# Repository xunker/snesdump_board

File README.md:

SNESDump Board
==============

A board for use with [https://github.com/cthill/SNESDump].

It is designed completely with through-hole components because that's what most people have lying
around.

The routing is _ugly_ because I wanted the board to be compatible with the original code without any
changes.

 ![Picture of rear of
board](images/snesdump_rear.jpg)

## Bill of Materials

* Cartridge Slot (1)
  - The cartridge slot can be either
    * A scavenged slot from a real SNES or Super-Famicom
    * A compatible 2.5mm 70-pin slot can be used with the appropriate pins yanked out
      - This slot *MUST* be 2.5mm pitch (so-called "metric spacing") and not the more common 2.54mm
    pitch (0.1 inches)

* Resistors (8)
  - Any 10K resistors will work as long as they can physically fit

* Shift Registers (3)
  - Any through-hole 74HC595N or compatible will work
  - Use of DIP sockets is recommended to make troubleshooting easier

* Arduino/Microcontroller
  - You can use either an Arduino Nano or Arduino Pro Micro (or clones thereof) in the indicated
    footprint
  - For obvious reasons you can't use both at the same time
  - It is **highly** recommended to mount the microcontroller on headers so it can be removed later

* Decoupling Capacitor (optional)
  - an electrolytic capacitor with a rating of at least 6.3v and a value from 0.1uF to 10uF will
    improve the general stability of the reader

## Licenses

SNES Slot Footprint ([SNES-CONN-EXP.kicad_mod](https://github.com/db-electronics/kicadlib)) is
distributed under the terms of CERN OHL v.1.2.

Arduino Pro Mini symbol and footprint (used as reference, not in final board output) is from
[SnapEDA](https://www.snapeda.com/parts/Arduino%20Pro%20Mini/Arduino/view-part/) and distributed
under [their license](footprints/SnapEDA+License.txt).

Unless otherwise specified, all other content herein is (C) 2022 Matthew Nielsen and is distributed
under the terms of [CC BY-NC-SA 4.0](https://creativecommons.org/licenses/by-nc-sa/4.0/).

### Sale of this board is NOT ALLOWED

I'm annoyed that I need to write this, but I do:

> ❗ ANY SALE OF THIS DESIGN IS STRICTLY PROHIBITED UNLESS AUTHORIZED IN WRITING BY RIGHTS HOLDER
>
> You **ARE ALLOWED** to make copies of this board for your __personal__ use, __give__ them to your
> friends, hand them out __for free__ to strangers on the street, or any other purpose so long as
> *you neither ask for nor receive payment* of any kind.
>
> You **ARE NOT ALLOWED** to make copies and sell them. Period. Whether you sell them for a profit
> or for a loss, it is not allowed. Whether you charge "for materials", "for time/labour", "for
> shipping and handling", it is not allowed.

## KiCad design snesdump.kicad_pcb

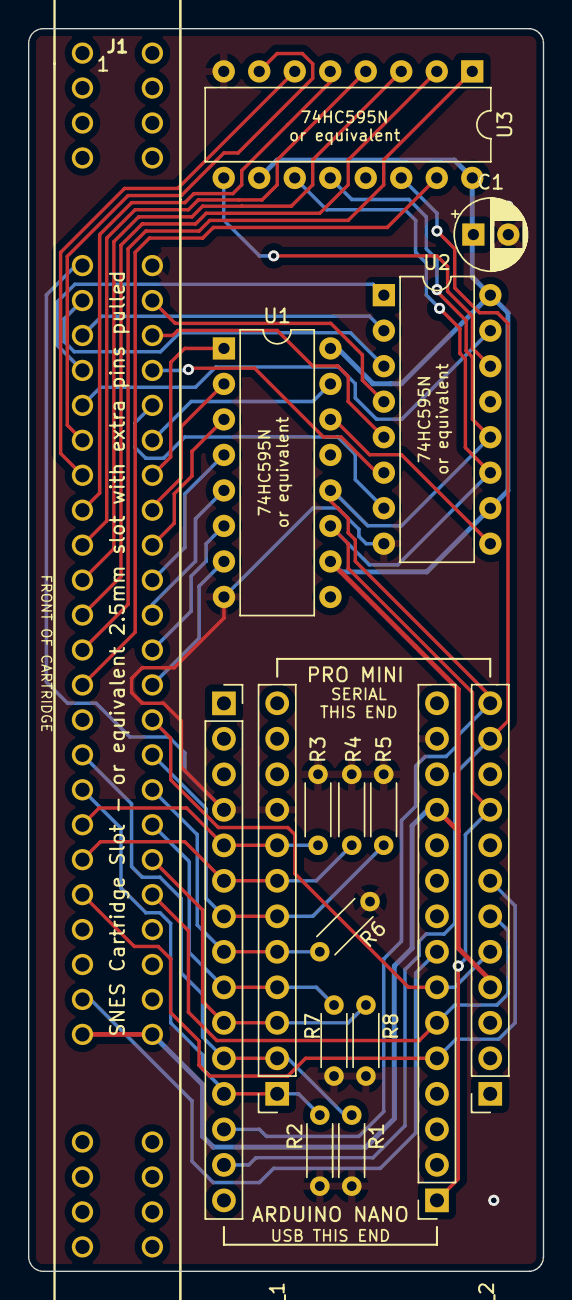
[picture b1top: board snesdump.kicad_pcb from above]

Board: 2 copper layers, 36.8 x 88.9 mm, 17 parts (0 on the bottom side), 43 nets.

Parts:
C1: 0.47uF; CP_Radial_D5.0mm_P2.50mm
J1: CARTRIDGE_SLOT; SNES-CONN-EXP
NANO_1, NANO_2: Conn_01x15_Male; PinSocket_1x15_P2.54mm_Vertical
PRO_MINI_1, PRO_MINI_2: Conn_01x12_Male; PinSocket_1x12_P2.54mm_Vertical
R1, R2, R3, R4, R5, R6, R7, R8: 10K; R_Axial_DIN0204_L3.6mm_D1.6mm_P5.08mm_Horizontal
U1, U2, U3: 74HC595; DIP-16_W7.62mm

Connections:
+5V: C1.1, J1.27, J1.58, NANO_2.12, PRO_MINI_2.4, U1.10 (~SRCLR), U1.16 (VCC), U2.10 (~SRCLR), U2.16 (VCC), U3.10 (~SRCLR), U3.16 (VCC)
A00: J1.17, U3.15 (QA)
A01: J1.16, U3.1 (QB)
A02: J1.15, U3.2 (QC)
A03: J1.14, U3.3 (QD)
A04: J1.13, U3.4 (QE)
A05: J1.12, U3.5 (QF)
A06: J1.11, U3.6 (QG)
A07: J1.10, U3.7 (QH)
A08: J1.9, U2.15 (QA)
A09: J1.8, U2.1 (QB)
A10: J1.7, U2.2 (QC)
A11: J1.6, U2.3 (QD)
A12: J1.37, U2.4 (QE)
A13: J1.38, U2.5 (QF)
A14: J1.39, U2.6 (QG)
A15: J1.40, U2.7 (QH)
BA0: J1.41, U1.15 (QA)
BA1: J1.42, U1.1 (QB)
BA2: J1.43, U1.2 (QC)
BA3: J1.44, U1.3 (QD)
BA4: J1.45, U1.4 (QE)
BA5: J1.46, U1.5 (QF)
BA6: J1.47, U1.6 (QG)
BA7: J1.48, U1.7 (QH)
D0: J1.19, NANO_1.11, PRO_MINI_1.2, R1.1
D1: J1.20, NANO_1.12, PRO_MINI_1.1, R2.1
D2: J1.21, NANO_1.5, PRO_MINI_1.8, R3.1
D3: J1.22, NANO_1.6, PRO_MINI_1.7, R4.1
D4: J1.50, NANO_1.7, PRO_MINI_1.6, R5.1
D5: J1.51, NANO_1.8, PRO_MINI_1.5, R6.1
D6: J1.52, NANO_1.9, PRO_MINI_1.4, R7.1
D7: J1.53, NANO_1.10, PRO_MINI_1.3, R8.1
GND: C1.2, J1.5, J1.36, NANO_1.4, NANO_2.14, PRO_MINI_1.9, R1.2, R2.2, R3.2, R4.2, R5.2, R6.2, R7.2, R8.2, U1.8 (GND), U2.8 (GND), U3.8 (GND)
RCK: NANO_1.13, PRO_MINI_2.12, U1.12 (RCLK), U2.12 (RCLK), U3.12 (RCLK)
SCK: NANO_2.1, PRO_MINI_2.9, U1.11 (SRCLK), U2.11 (SRCLK), U3.11 (SRCLK)
SER_1_2: U1.14 (SER), U2.9 (QH')
SER_2_3: U2.14 (SER), U3.9 (QH')
SER_3_D11: NANO_1.14, PRO_MINI_2.11, U3.14 (SER)
/CS: J1.49, NANO_2.7, PRO_MINI_2.5
/RD: J1.23, NANO_2.5, PRO_MINI_2.7
/RESET: J1.26, NANO_2.8
/WR: J1.54, NANO_2.6, PRO_MINI_2.6

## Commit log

2022-10-11 add note about decoupling capacitor

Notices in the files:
snesdump.kicad_pcb:
Board (C) 2022 - Matthew Nielsen
